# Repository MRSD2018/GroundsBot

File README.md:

# GroundsBot
A ~~flexible~~ system that can perform regular outdoor grounds maintenance tasks such a ~~sidewalk sweeping~~,
~~snow clearing~~ or grass cutting on extreme terrain for use by grounds care ~~and snow removal~~ companies.

This repository is for electrical and mechanical design.  For actual code running on GroundsBot, checkout: https://github.com/MRSD2018/GroundsBot-Software

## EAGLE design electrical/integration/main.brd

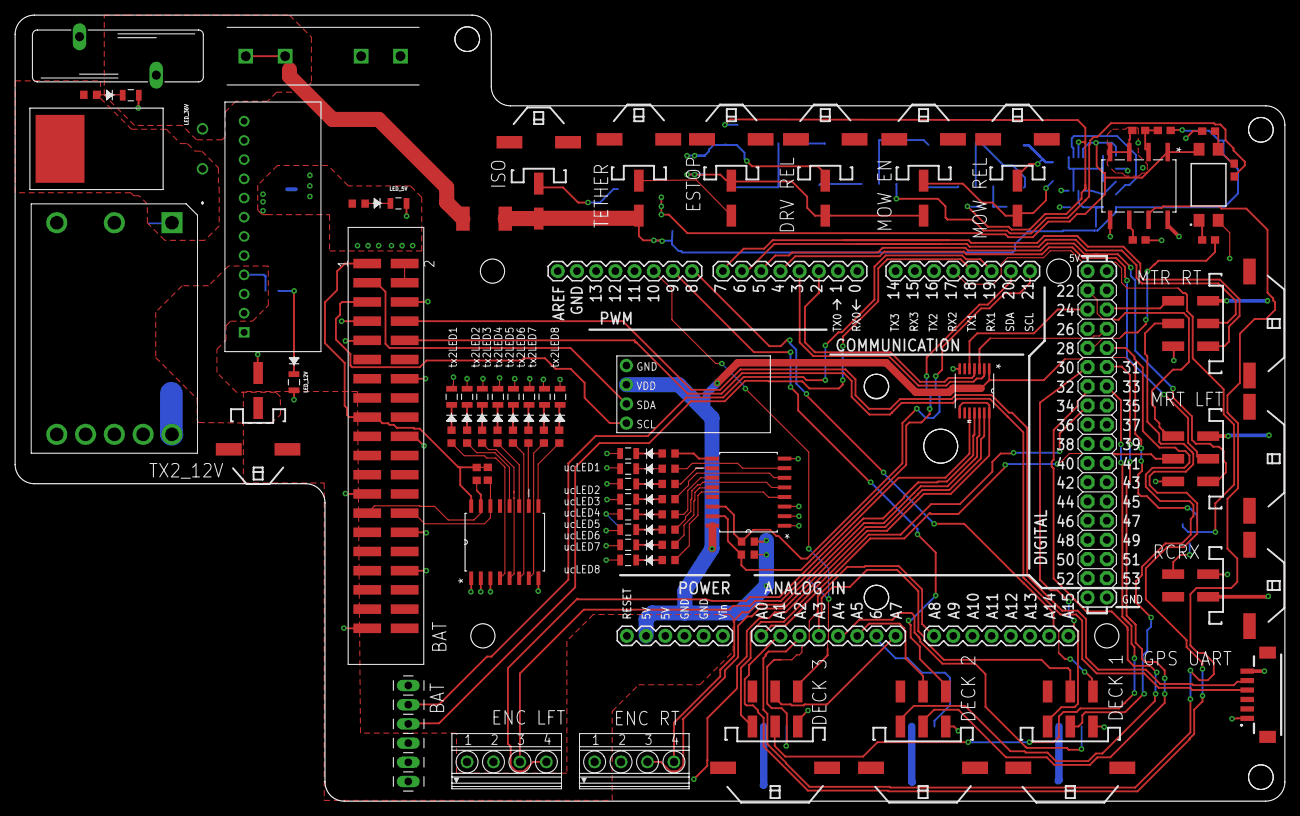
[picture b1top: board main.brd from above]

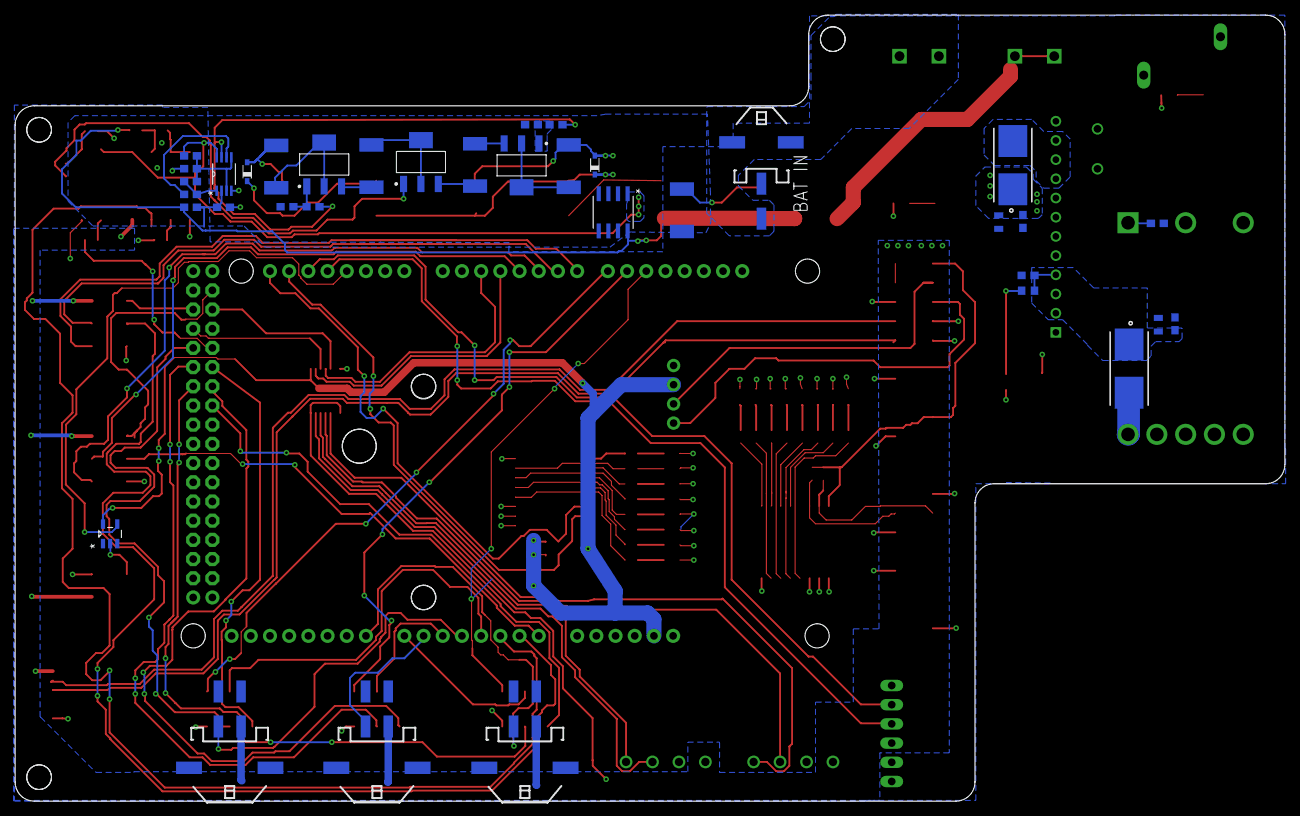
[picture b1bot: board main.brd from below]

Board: 2 copper layers, 168.0 x 104.0 mm, 114 parts (36 on the bottom side), 116 nets.

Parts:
JETSON1:JETSON_J17_UART1:JP3: 61300611121; 1X06
JETSON1:JETSON_TX2_J21_EXPANSION1:LED1, JETSON1:JETSON_TX2_J21_EXPANSION1:LED2, JETSON1:JETSON_TX2_J21_EXPANSION1:LED3, JETSON1:JETSON_TX2_J21_EXPANSION1:LED4, JETSON1:JETSON_TX2_J21_EXPANSION1:LED5, JETSON1:JETSON_TX2_J21_EXPANSION1:LED6, JETSON1:JETSON_TX2_J21_EXPANSION1:LED7, JETSON1:JETSON_TX2_J21_EXPANSION1:LED8: CMD17-21VGD_TR8; LED_CMD17-21VGD_TR8
JETSON1:JETSON_TX2_J21_EXPANSION1:R1, JETSON1:JETSON_TX2_J21_EXPANSION1:R2, JETSON1:JETSON_TX2_J21_EXPANSION1:R3, JETSON1:JETSON_TX2_J21_EXPANSION1:R4, JETSON1:JETSON_TX2_J21_EXPANSION1:R5, JETSON1:JETSON_TX2_J21_EXPANSION1:R6, JETSON1:JETSON_TX2_J21_EXPANSION1:R7, JETSON1:JETSON_TX2_J21_EXPANSION1:R8: 60; R0603
JETSON1:JETSON_TX2_J21_EXPANSION1:R9, JETSON1:JETSON_TX2_J21_EXPANSION1:R10: 10k; R0603
JETSON1:JETSON_TX2_J21_EXPANSION1:U1: PCF8574ATD; SOIC127P1032X265-16N
JETSON1:JETSON_TX2_J21_EXPANSION1:U$3: TSM-120-XX-XXX-DV; TSM-120-XX-XXX-D
MICROCONTROLLER1:LED1, MICROCONTROLLER1:LED2, MICROCONTROLLER1:LED3, MICROCONTROLLER1:LED4, MICROCONTROLLER1:LED5, MICROCONTROLLER1:LED6, MICROCONTROLLER1:LED7, MICROCONTROLLER1:LED8: CMD17-21VGD_TR8; LED_CMD17-21VGD_TR8
MICROCONTROLLER1:R1, MICROCONTROLLER1:R2, MICROCONTROLLER1:R3, MICROCONTROLLER1:R4, MICROCONTROLLER1:R5, MICROCONTROLLER1:R6, MICROCONTROLLER1:R7, MICROCONTROLLER1:R8: 60; R0603
MICROCONTROLLER1:R9, MICROCONTROLLER1:R10: 10k; R0603
MICROCONTROLLER1:U1: PCF8574ATD; SOIC127P1032X265-16N
MICROCONTROLLER1:U$1: ARDUINO_MEGA_R3FULL; ARDUINO_MEGA
MOTOR_TOP1:JDL, MOTOR_TOP1:JDR, MOTOR_TOP1:X3, MOTOR_TOP1:X4, MOTOR_TOP1:X5: 43045-0609
MOTOR_TOP1:X6, MOTOR_TOP1:X7, MOTOR_TOP1:X8: 43045-0409
POWER_TOP1:C1, POWER_TOP1:C3: 1uF; C0603
POWER_TOP1:C2, POWER_TOP1:C4: 100uF; C0603
POWER_TOP1:F1, POWER_TOP1:F2: 0154004.DR; FUSE_0154004.DR
POWER_TOP1:LED1, POWER_TOP1:LED2, POWER_TOP1:LED3: CMD17-21VGD_TR8; LED_CMD17-21VGD_TR8
POWER_TOP1:MOV1: AVR-M2012C120MT6AB; 0805
POWER_TOP1:MOV2: VC080503A100DP; 0805
POWER_TOP1:R2: 495; R0603
POWER_TOP1:R3: 145; R0603
POWER_TOP1:R4: 1695; R0603
POWER_TOP1:U$1: R-745.0P; SIP-12
POWER_TOP1:U$2: V36SE12004NRFA; V36SE12004NRFA-TH
RC_INPUT1:U1: NC7SZ04M5; SOT95P280X145-5N
RC_INPUT1:X1: 43045-0409
RELAY_CONTROL_TOP1:D2: STPS20M60D; TO220AC
RELAY_CONTROL_TOP1:FH3: FUSE_HOLDER_0.205X0.787IN; LF445_0.807IN
RELAY_CONTROL_TOP1:ISO1:R1, RELAY_CONTROL_TOP1:RELAY_CONTROL1:R11, RELAY_CONTROL_TOP1:RELAY_CONTROL1:R13, RELAY_CONTROL_TOP1:RELAY_CONTROL1:UVLO1:R4: 47k; 0603
RELAY_CONTROL_TOP1:ISO1:R2, RELAY_CONTROL_TOP1:ISO1:R5: 330k; 0603
RELAY_CONTROL_TOP1:ISO1:R3, RELAY_CONTROL_TOP1:ISO1:R4, RELAY_CONTROL_TOP1:RELAY_CONTROL1:R1, RELAY_CONTROL_TOP1:RELAY_CONTROL1:R3: 1.20k; 0603
RELAY_CONTROL_TOP1:ISO1:R6: 2.0k; 0603
RELAY_CONTROL_TOP1:ISO1:U1: AMC1200SDUB; DUB8
RELAY_CONTROL_TOP1:ISO1:U2: SFH615A-3X009T; SOIC254P1016X390-4N
RELAY_CONTROL_TOP1:JBAT, RELAY_CONTROL_TOP1:JDC, RELAY_CONTROL_TOP1:JISO, RELAY_CONTROL_TOP1:JMC, RELAY_CONTROL_TOP1:RELAY_CONTROL1:JESTP, RELAY_CONTROL_TOP1:RELAY_CONTROL1:JMOW, RELAY_CONTROL_TOP1:RELAY_CONTROL1:JTHR: 43045-0209
RELAY_CONTROL_TOP1:MOV1: MOV-20D470K; S20K440
RELAY_CONTROL_TOP1:R1, RELAY_CONTROL_TOP1:R2: RES_0R_2512_1W; R2512
RELAY_CONTROL_TOP1:REGULATOR1:U1: LM2936HVMAX-5.0/NOPB; M08A
RELAY_CONTROL_TOP1:RELAY_CONTROL1:D1, RELAY_CONTROL_TOP1:RELAY_CONTROL1:D2: 1N4148WSTR; SOD323_ST
RELAY_CONTROL_TOP1:RELAY_CONTROL1:RCCB1, RELAY_CONTROL_TOP1:RELAY_CONTROL1:RCCB2, RELAY_CONTROL_TOP1:RELAY_CONTROL1:RCCD, RELAY_CONTROL_TOP1:RELAY_CONTROL1:RCCM: RES_52R3_2512_1W_1%; R2512
RELAY_CONTROL_TOP1:RELAY_CONTROL1:U$2, RELAY_CONTROL_TOP1:RELAY_CONTROL1:U$7, RELAY_CONTROL_TOP1:RELAY_CONTROL1:U$10: ZXTN25100DGTA; SOT230P700X160-4N
RELAY_CONTROL_TOP1:RELAY_CONTROL1:UVLO1:R1: 750K; 0603
RELAY_CONTROL_TOP1:RELAY_CONTROL1:UVLO1:R2: 150k; 0603
RELAY_CONTROL_TOP1:RELAY_CONTROL1:UVLO1:R3: 180k; 0603
RELAY_CONTROL_TOP1:RELAY_CONTROL1:UVLO1:R7: 6.8k; 0603
RELAY_CONTROL_TOP1:RELAY_CONTROL1:UVLO1:R8: 75k; 0603
RELAY_CONTROL_TOP1:RELAY_CONTROL1:UVLO1:U1: LMV762MM; SOP65P490X110-8N
SENSOR_TOP1:ENCODER1:X1, SENSOR_TOP1:ENCODER2:X1: 1751264
SENSOR_TOP1:IMU1:U$1: LSM9DS1; SPARKFUN-9DOF-BREAKOUT
SENSOR_TOP1:REACH_GPS1:U$1: DF13-6P-1.25V; DF13C-6P-1.25V
U301: LSF0204PWR; SOP65P640X120-14N
X101: 43045-0209

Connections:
3V3: MICROCONTROLLER1:R9.2, MICROCONTROLLER1:R10.2, MICROCONTROLLER1:U1.16, MICROCONTROLLER1:U$1.3.3V, RC_INPUT1:U1.5, SENSOR_TOP1:IMU1:U$1.VDD, U301.1
5V: MOTOR_TOP1:JDL.P$1, MOTOR_TOP1:JDR.P$1, MOTOR_TOP1:X6.P$1, MOTOR_TOP1:X7.P$1, MOTOR_TOP1:X8.P$1, POWER_TOP1:C4.1, POWER_TOP1:F1.1, POWER_TOP1:MOV2.1, POWER_TOP1:R3.2, RC_INPUT1:X1.P$2, RELAY_CONTROL_TOP1:ISO1:U1.8, SENSOR_TOP1:ENCODER1:X1.1, SENSOR_TOP1:ENCODER2:X1.1, SENSOR_TOP1:REACH_GPS1:U$1.P$6, U301.8, U301.14
5V_ISO: RELAY_CONTROL_TOP1:ISO1:U1.1, RELAY_CONTROL_TOP1:ISO1:U2.4, RELAY_CONTROL_TOP1:REGULATOR1:U1.1, RELAY_CONTROL_TOP1:RELAY_CONTROL1:UVLO1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.2, RELAY_CONTROL_TOP1:RELAY_CONTROL1:UVLO1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.8
12V: MICROCONTROLLER1:U$1.VIN, POWER_TOP1:C2.1, POWER_TOP1:C3.1, POWER_TOP1:F2.1, POWER_TOP1:MOV1.1, POWER_TOP1:R2.2, POWER_TOP1:U$1.VIN1, POWER_TOP1:U$1.VIN2, POWER_TOP1:U$1.VIN3, X101.P$1
36V: POWER_TOP1:C1.1, POWER_TOP1:R4.2, POWER_TOP1:U$2.+VIN, RELAY_CONTROL_TOP1:D2.1, RELAY_CONTROL_TOP1:D2.2
GND: JETSON1:JETSON_J17_UART1:JP3.1, JETSON1:JETSON_TX2_J21_EXPANSION1:LED1.2, JETSON1:JETSON_TX2_J21_EXPANSION1:LED2.2, JETSON1:JETSON_TX2_J21_EXPANSION1:LED3.2, JETSON1:JETSON_TX2_J21_EXPANSION1:LED4.2, JETSON1:JETSON_TX2_J21_EXPANSION1:LED5.2, JETSON1:JETSON_TX2_J21_EXPANSION1:LED6.2, JETSON1:JETSON_TX2_J21_EXPANSION1:LED7.2, JETSON1:JETSON_TX2_J21_EXPANSION1:LED8.2, JETSON1:JETSON_TX2_J21_EXPANSION1:U1.1, JETSON1:JETSON_TX2_J21_EXPANSION1:U1.2, JETSON1:JETSON_TX2_J21_EXPANSION1:U1.3, JETSON1:JETSON_TX2_J21_EXPANSION1:U1.8, JETSON1:JETSON_TX2_J21_EXPANSION1:U$3.6, JETSON1:JETSON_TX2_J21_EXPANSION1:U$3.9, JETSON1:JETSON_TX2_J21_EXPANSION1:U$3.14, JETSON1:JETSON_TX2_J21_EXPANSION1:U$3.20, JETSON1:JETSON_TX2_J21_EXPANSION1:U$3.25, JETSON1:JETSON_TX2_J21_EXPANSION1:U$3.30, JETSON1:JETSON_TX2_J21_EXPANSION1:U$3.34, JETSON1:JETSON_TX2_J21_EXPANSION1:U$3.39, MICROCONTROLLER1:LED1.2, MICROCONTROLLER1:LED2.2, MICROCONTROLLER1:LED3.2, MICROCONTROLLER1:LED4.2, MICROCONTROLLER1:LED5.2, MICROCONTROLLER1:LED6.2, MICROCONTROLLER1:LED7.2, MICROCONTROLLER1:LED8.2, MICROCONTROLLER1:U1.1, MICROCONTROLLER1:U1.2, MICROCONTROLLER1:U1.3, MICROCONTROLLER1:U1.8, MICROCONTROLLER1:U$1.GND@0, MICROCONTROLLER1:U$1.GND@1, MICROCONTROLLER1:U$1.GND@2, MICROCONTROLLER1:U$1.GND@3, MICROCONTROLLER1:U$1.GND@4, MOTOR_TOP1:JDL.P$6, MOTOR_TOP1:JDR.P$6, MOTOR_TOP1:X3.P$1, MOTOR_TOP1:X4.P$1, MOTOR_TOP1:X5.P$1, MOTOR_TOP1:X6.P$3, MOTOR_TOP1:X7.P$3, MOTOR_TOP1:X8.P$3, POWER_TOP1:C1.2, POWER_TOP1:C2.2, POWER_TOP1:C3.2, POWER_TOP1:C4.2, POWER_TOP1:LED1.2, POWER_TOP1:LED2.2, POWER_TOP1:LED3.2, POWER_TOP1:MOV1.2, POWER_TOP1:MOV2.2, POWER_TOP1:U$1.ENABLE, POWER_TOP1:U$1.GND1, POWER_TOP1:U$1.GND2, POWER_TOP1:U$1.GND3, POWER_TOP1:U$1.GND4, POWER_TOP1:U$2.-VIN, POWER_TOP1:U$2.-VOUT, POWER_TOP1:U$2.ENABLE, RC_INPUT1:U1.3, RC_INPUT1:X1.P$1, RELAY_CONTROL_TOP1:ISO1:R2.1, RELAY_CONTROL_TOP1:ISO1:U1.5, RELAY_CONTROL_TOP1:ISO1:U2.2, RELAY_CONTROL_TOP1:JBAT.P$1, RELAY_CONTROL_TOP1:MOV1.2, RELAY_CONTROL_TOP1:R1.2, SENSOR_TOP1:ENCODER1:X1.2, SENSOR_TOP1:ENCODER2:X1.2, SENSOR_TOP1:IMU1:U$1.GND, SENSOR_TOP1:REACH_GPS1:U$1.P$1, U301.7, X101.P$2
GND_ISO: RELAY_CONTROL_TOP1:ISO1:R1.1, RELAY_CONTROL_TOP1:ISO1:R6.1, RELAY_CONTROL_TOP1:ISO1:U1.3, RELAY_CONTROL_TOP1:ISO1:U1.4, RELAY_CONTROL_TOP1:JISO.P$1, RELAY_CONTROL_TOP1:R1.1, RELAY_CONTROL_TOP1:REGULATOR1:U1.2, RELAY_CONTROL_TOP1:REGULATOR1:U1.3, RELAY_CONTROL_TOP1:REGULATOR1:U1.6, RELAY_CONTROL_TOP1:REGULATOR1:U1.7, RELAY_CONTROL_TOP1:RELAY_CONTROL1:R11.2, RELAY_CONTROL_TOP1:RELAY_CONTROL1:R13.2, RELAY_CONTROL_TOP1:RELAY_CONTROL1:RCCD.1, RELAY_CONTROL_TOP1:RELAY_CONTROL1:U$2.3, RELAY_CONTROL_TOP1:RELAY_CONTROL1:UVLO1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.1, RELAY_CONTROL_TOP1:RELAY_CONTROL1:UVLO1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.1, RELAY_CONTROL_TOP1:RELAY_CONTROL1:UVLO1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.4
JETSON1:JETSON_TX2_J21_EXPANSION1:I2C_GP1_CLK_3V3: JETSON1:JETSON_TX2_J21_EXPANSION1:R10.1, JETSON1:JETSON_TX2_J21_EXPANSION1:U1.14, JETSON1:JETSON_TX2_J21_EXPANSION1:U$3.28
JETSON1:JETSON_TX2_J21_EXPANSION1:I2C_GP1_DAT_3V3: JETSON1:JETSON_TX2_J21_EXPANSION1:R9.1, JETSON1:JETSON_TX2_J21_EXPANSION1:U1.15, JETSON1:JETSON_TX2_J21_EXPANSION1:U$3.27
JETSON1:JETSON_TX2_J21_EXPANSION1:N$1: JETSON1:JETSON_TX2_J21_EXPANSION1:LED8.1, JETSON1:JETSON_TX2_J21_EXPANSION1:R8.1
JETSON1:JETSON_TX2_J21_EXPANSION1:N$2: JETSON1:JETSON_TX2_J21_EXPANSION1:LED7.1, JETSON1:JETSON_TX2_J21_EXPANSION1:R7.1
JETSON1:JETSON_TX2_J21_EXPANSION1:N$3: JETSON1:JETSON_TX2_J21_EXPANSION1:LED6.1, JETSON1:JETSON_TX2_J21_EXPANSION1:R6.1
JETSON1:JETSON_TX2_J21_EXPANSION1:N$4: JETSON1:JETSON_TX2_J21_EXPANSION1:LED5.1, JETSON1:JETSON_TX2_J21_EXPANSION1:R5.1
JETSON1:JETSON_TX2_J21_EXPANSION1:N$5: JETSON1:JETSON_TX2_J21_EXPANSION1:LED4.1, JETSON1:JETSON_TX2_J21_EXPANSION1:R4.1
JETSON1:JETSON_TX2_J21_EXPANSION1:N$6: JETSON1:JETSON_TX2_J21_EXPANSION1:LED3.1, JETSON1:JETSON_TX2_J21_EXPANSION1:R3.1
JETSON1:JETSON_TX2_J21_EXPANSION1:N$7: JETSON1:JETSON_TX2_J21_EXPANSION1:LED2.1, JETSON1:JETSON_TX2_J21_EXPANSION1:R2.1
JETSON1:JETSON_TX2_J21_EXPANSION1:N$8: JETSON1:JETSON_TX2_J21_EXPANSION1:LED1.1, JETSON1:JETSON_TX2_J21_EXPANSION1:R1.1
JETSON1:JETSON_TX2_J21_EXPANSION1:N$9: JETSON1:JETSON_TX2_J21_EXPANSION1:R8.2, JETSON1:JETSON_TX2_J21_EXPANSION1:U1.12
JETSON1:JETSON_TX2_J21_EXPANSION1:N$10: JETSON1:JETSON_TX2_J21_EXPANSION1:R7.2, JETSON1:JETSON_TX2_J21_EXPANSION1:U1.11
JETSON1:JETSON_TX2_J21_EXPANSION1:N$11: JETSON1:JETSON_TX2_J21_EXPANSION1:R6.2, JETSON1:JETSON_TX2_J21_EXPANSION1:U1.10
JETSON1:JETSON_TX2_J21_EXPANSION1:N$12: JETSON1:JETSON_TX2_J21_EXPANSION1:R5.2, JETSON1:JETSON_TX2_J21_EXPANSION1:U1.9
JETSON1:JETSON_TX2_J21_EXPANSION1:N$13: JETSON1:JETSON_TX2_J21_EXPANSION1:R4.2, JETSON1:JETSON_TX2_J21_EXPANSION1:U1.7
JETSON1:JETSON_TX2_J21_EXPANSION1:N$14: JETSON1:JETSON_TX2_J21_EXPANSION1:R3.2, JETSON1:JETSON_TX2_J21_EXPANSION1:U1.6
JETSON1:JETSON_TX2_J21_EXPANSION1:N$15: JETSON1:JETSON_TX2_J21_EXPANSION1:R2.2, JETSON1:JETSON_TX2_J21_EXPANSION1:U1.5
JETSON1:JETSON_TX2_J21_EXPANSION1:N$16: JETSON1:JETSON_TX2_J21_EXPANSION1:R1.2, JETSON1:JETSON_TX2_J21_EXPANSION1:U1.4
JETSON1:JETSON_TX2_J21_EXPANSION1:VDD_3V3_SYS: JETSON1:JETSON_TX2_J21_EXPANSION1:R9.2, JETSON1:JETSON_TX2_J21_EXPANSION1:R10.2, JETSON1:JETSON_TX2_J21_EXPANSION1:U1.16, JETSON1:JETSON_TX2_J21_EXPANSION1:U$3.1, JETSON1:JETSON_TX2_J21_EXPANSION1:U$3.17
JETSON1:JETSON_TX2_J21_EXPANSION1:VDD_5V0_IO_SYS: JETSON1:JETSON_TX2_J21_EXPANSION1:U$3.2, JETSON1:JETSON_TX2_J21_EXPANSION1:U$3.4
MICROCONTROLLER1:LED_SCL: MICROCONTROLLER1:R10.1, MICROCONTROLLER1:U1.14, MICROCONTROLLER1:U$1.21
MICROCONTROLLER1:LED_SDA: MICROCONTROLLER1:R9.1, MICROCONTROLLER1:U1.15, MICROCONTROLLER1:U$1.20
MICROCONTROLLER1:N$1: MICROCONTROLLER1:LED8.1, MICROCONTROLLER1:R8.1
MICROCONTROLLER1:N$2: MICROCONTROLLER1:R1.2, MICROCONTROLLER1:U1.4
MICROCONTROLLER1:N$3: MICROCONTROLLER1:LED7.1, MICROCONTROLLER1:R7.1
MICROCONTROLLER1:N$12: MICROCONTROLLER1:LED6.1, MICROCONTROLLER1:R6.1
MICROCONTROLLER1:N$13: MICROCONTROLLER1:LED5.1, MICROCONTROLLER1:R5.1
MICROCONTROLLER1:N$14: MICROCONTROLLER1:LED4.1, MICROCONTROLLER1:R4.1
MICROCONTROLLER1:N$15: MICROCONTROLLER1:LED3.1, MICROCONTROLLER1:R3.1
MICROCONTROLLER1:N$16: MICROCONTROLLER1:LED2.1, MICROCONTROLLER1:R2.1
MICROCONTROLLER1:N$17: MICROCONTROLLER1:LED1.1, MICROCONTROLLER1:R1.1
MICROCONTROLLER1:N$18: MICROCONTROLLER1:R8.2, MICROCONTROLLER1:U1.12
MICROCONTROLLER1:N$19: MICROCONTROLLER1:R7.2, MICROCONTROLLER1:U1.11
MICROCONTROLLER1:N$20: MICROCONTROLLER1:R6.2, MICROCONTROLLER1:U1.10
MICROCONTROLLER1:N$21: MICROCONTROLLER1:R5.2, MICROCONTROLLER1:U1.9
MICROCONTROLLER1:N$22: MICROCONTROLLER1:R4.2, MICROCONTROLLER1:U1.7
MICROCONTROLLER1:N$23: MICROCONTROLLER1:R3.2, MICROCONTROLLER1:U1.6
MICROCONTROLLER1:N$24: MICROCONTROLLER1:R2.2, MICROCONTROLLER1:U1.5
MOW_EN: MICROCONTROLLER1:U$1.28, RELAY_CONTROL_TOP1:ISO1:R3.2
unnamed: MICROCONTROLLER1:U$1.7, MOTOR_TOP1:JDR.P$3
unnamed: JETSON1:JETSON_TX2_J21_EXPANSION1:U$3.10, SENSOR_TOP1:REACH_GPS1:U$1.P$4
unnamed: MICROCONTROLLER1:U$1.22, MOTOR_TOP1:JDL.P$4
unnamed: MICROCONTROLLER1:U$1.A0, MOTOR_TOP1:JDL.P$5
unnamed: MICROCONTROLLER1:U$1.6, MOTOR_TOP1:JDR.P$2
unnamed: JETSON1:JETSON_TX2_J21_EXPANSION1:U$3.8, SENSOR_TOP1:REACH_GPS1:U$1.P$5
unnamed: MICROCONTROLLER1:U$1.25, MOTOR_TOP1:JDR.P$4
unnamed: MICROCONTROLLER1:U$1.A1, MOTOR_TOP1:JDR.P$5
unnamed: MICROCONTROLLER1:U$1.33, MOTOR_TOP1:X5.P$2
unnamed: MICROCONTROLLER1:U$1.34, MOTOR_TOP1:X5.P$3
unnamed: MICROCONTROLLER1:U$1.10, MOTOR_TOP1:X5.P$4
unnamed: MICROCONTROLLER1:U$1.A8, MOTOR_TOP1:X8.P$2
unnamed: MICROCONTROLLER1:U$1.A7, MOTOR_TOP1:X5.P$5
unnamed: MICROCONTROLLER1:U$1.A6, MOTOR_TOP1:X7.P$2
unnamed: MICROCONTROLLER1:U$1.A5, MOTOR_TOP1:X4.P$5
unnamed: MICROCONTROLLER1:U$1.9, MOTOR_TOP1:X4.P$4
unnamed: MICROCONTROLLER1:U$1.32, MOTOR_TOP1:X4.P$3
unnamed: MICROCONTROLLER1:U$1.31, MOTOR_TOP1:X4.P$2
unnamed: JETSON1:JETSON_TX2_J21_EXPANSION1:U$3.5, SENSOR_TOP1:IMU1:U$1.SCL
unnamed: JETSON1:JETSON_TX2_J21_EXPANSION1:U$3.3, SENSOR_TOP1:IMU1:U$1.SDA
unnamed: MICROCONTROLLER1:U$1.A4, MOTOR_TOP1:X6.P$2
unnamed: MICROCONTROLLER1:U$1.A3, MOTOR_TOP1:X3.P$5
unnamed: MICROCONTROLLER1:U$1.8, MOTOR_TOP1:X3.P$4
unnamed: MICROCONTROLLER1:U$1.30, MOTOR_TOP1:X3.P$3
unnamed: MICROCONTROLLER1:U$1.29, MOTOR_TOP1:X3.P$2
unnamed: MICROCONTROLLER1:U$1.5, MOTOR_TOP1:JDL.P$3
unnamed: MICROCONTROLLER1:U$1.4, MOTOR_TOP1:JDL.P$2
unnamed: JETSON1:JETSON_J17_UART1:JP3.5, MICROCONTROLLER1:U$1.19
unnamed: JETSON1:JETSON_J17_UART1:JP3.4, MICROCONTROLLER1:U$1.18
unnamed: MICROCONTROLLER1:U$1.17, RC_INPUT1:U1.4
unnamed: MICROCONTROLLER1:U$1.2, U301.4
unnamed: MICROCONTROLLER1:U$1.24, U301.5
unnamed: MICROCONTROLLER1:U$1.3, U301.2
unnamed: MICROCONTROLLER1:U$1.27, U301.3
POWER_TOP1:N$1: POWER_TOP1:F2.2, POWER_TOP1:U$2.+VOUT
POWER_TOP1:N$2: POWER_TOP1:F1.2, POWER_TOP1:U$1.VOUT1, POWER_TOP1:U$1.VOUT2, POWER_TOP1:U$1.VOUT3
POWER_TOP1:N$3: POWER_TOP1:LED1.1, POWER_TOP1:R4.1
POWER_TOP1:N$4: POWER_TOP1:LED2.1, POWER_TOP1:R2.1
POWER_TOP1:N$5: POWER_TOP1:LED3.1, POWER_TOP1:R3.1
RC_INPUT1:SBUS_SIG_IN: RC_INPUT1:U1.2, RC_INPUT1:X1.P$3
RELAY_CONTROL_TOP1:36V_RAW: RELAY_CONTROL_TOP1:ISO1:R5.2, RELAY_CONTROL_TOP1:JISO.P$2, RELAY_CONTROL_TOP1:R2.1, RELAY_CONTROL_TOP1:REGULATOR1:U1.8, RELAY_CONTROL_TOP1:RELAY_CONTROL1:JTHR.P$2, RELAY_CONTROL_TOP1:RELAY_CONTROL1:UVLO1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.2
RELAY_CONTROL_TOP1:ISO1:N$1: RELAY_CONTROL_TOP1:ISO1:R2.2, RELAY_CONTROL_TOP1:ISO1:U1.6
RELAY_CONTROL_TOP1:ISO1:N$2: RELAY_CONTROL_TOP1:ISO1:R5.1, RELAY_CONTROL_TOP1:ISO1:R6.2, RELAY_CONTROL_TOP1:ISO1:U1.2
RELAY_CONTROL_TOP1:ISO1:N$3: RELAY_CONTROL_TOP1:ISO1:R1.2, RELAY_CONTROL_TOP1:ISO1:R4.2, RELAY_CONTROL_TOP1:ISO1:U2.3
RELAY_CONTROL_TOP1:ISO1:N$4: RELAY_CONTROL_TOP1:ISO1:R3.1, RELAY_CONTROL_TOP1:ISO1:U2.1
RELAY_CONTROL_TOP1:N$1: RELAY_CONTROL_TOP1:FH3.1, RELAY_CONTROL_TOP1:FH3.2, RELAY_CONTROL_TOP1:JBAT.P$2
RELAY_CONTROL_TOP1:N$2: RELAY_CONTROL_TOP1:JMC.P$2, RELAY_CONTROL_TOP1:RELAY_CONTROL1:D2.C, RELAY_CONTROL_TOP1:RELAY_CONTROL1:JMOW.P$1
RELAY_CONTROL_TOP1:N$3: RELAY_CONTROL_TOP1:JDC.P$2, RELAY_CONTROL_TOP1:RELAY_CONTROL1:D1.C, RELAY_CONTROL_TOP1:RELAY_CONTROL1:JESTP.P$1, RELAY_CONTROL_TOP1:RELAY_CONTROL1:JMOW.P$2
RELAY_CONTROL_TOP1:N$4: RELAY_CONTROL_TOP1:JMC.P$1, RELAY_CONTROL_TOP1:RELAY_CONTROL1:D2.A, RELAY_CONTROL_TOP1:RELAY_CONTROL1:RCCB2.2
RELAY_CONTROL_TOP1:N$5: RELAY_CONTROL_TOP1:ISO1:R4.1, RELAY_CONTROL_TOP1:RELAY_CONTROL1:U$2.1
RELAY_CONTROL_TOP1:N$6: RELAY_CONTROL_TOP1:JDC.P$1, RELAY_CONTROL_TOP1:RELAY_CONTROL1:D1.A, RELAY_CONTROL_TOP1:RELAY_CONTROL1:RCCB1.2
RELAY_CONTROL_TOP1:N$11: RELAY_CONTROL_TOP1:D2.3, RELAY_CONTROL_TOP1:FH3.3, RELAY_CONTROL_TOP1:FH3.4, RELAY_CONTROL_TOP1:MOV1.1, RELAY_CONTROL_TOP1:R2.2
RELAY_CONTROL_TOP1:RELAY_CONTROL1:!UVLO!: RELAY_CONTROL_TOP1:RELAY_CONTROL1:R1.1, RELAY_CONTROL_TOP1:RELAY_CONTROL1:R3.1, RELAY_CONTROL_TOP1:RELAY_CONTROL1:UVLO1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.7
RELAY_CONTROL_TOP1:RELAY_CONTROL1:N$1: RELAY_CONTROL_TOP1:RELAY_CONTROL1:JESTP.P$2, RELAY_CONTROL_TOP1:RELAY_CONTROL1:JTHR.P$1
RELAY_CONTROL_TOP1:RELAY_CONTROL1:N$2: RELAY_CONTROL_TOP1:RELAY_CONTROL1:RCCM.1, RELAY_CONTROL_TOP1:RELAY_CONTROL1:U$2.2, RELAY_CONTROL_TOP1:RELAY_CONTROL1:U$2.4
RELAY_CONTROL_TOP1:RELAY_CONTROL1:N$5: RELAY_CONTROL_TOP1:RELAY_CONTROL1:RCCB2.1, RELAY_CONTROL_TOP1:RELAY_CONTROL1:U$7.2, RELAY_CONTROL_TOP1:RELAY_CONTROL1:U$7.4
RELAY_CONTROL_TOP1:RELAY_CONTROL1:N$6: RELAY_CONTROL_TOP1:RELAY_CONTROL1:RCCM.2, RELAY_CONTROL_TOP1:RELAY_CONTROL1:U$7.3
RELAY_CONTROL_TOP1:RELAY_CONTROL1:N$7: RELAY_CONTROL_TOP1:RELAY_CONTROL1:R3.2, RELAY_CONTROL_TOP1:RELAY_CONTROL1:R11.1, RELAY_CONTROL_TOP1:RELAY_CONTROL1:U$10.1
RELAY_CONTROL_TOP1:RELAY_CONTROL1:N$9: RELAY_CONTROL_TOP1:RELAY_CONTROL1:RCCD.2, RELAY_CONTROL_TOP1:RELAY_CONTROL1:U$10.3
RELAY_CONTROL_TOP1:RELAY_CONTROL1:N$10: RELAY_CONTROL_TOP1:RELAY_CONTROL1:RCCB1.1, RELAY_CONTROL_TOP1:RELAY_CONTROL1:U$10.2, RELAY_CONTROL_TOP1:RELAY_CONTROL1:U$10.4
RELAY_CONTROL_TOP1:RELAY_CONTROL1:N$11: RELAY_CONTROL_TOP1:RELAY_CONTROL1:R1.2, RELAY_CONTROL_TOP1:RELAY_CONTROL1:R13.1, RELAY_CONTROL_TOP1:RELAY_CONTROL1:U$7.1
RELAY_CONTROL_TOP1:RELAY_CONTROL1:UVLO1:N$2: RELAY_CONTROL_TOP1:RELAY_CONTROL1:UVLO1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.1, RELAY_CONTROL_TOP1:RELAY_CONTROL1:UVLO1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.6
RELAY_CONTROL_TOP1:RELAY_CONTROL1:UVLO1:N$3: RELAY_CONTROL_TOP1:RELAY_CONTROL1:UVLO1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.1, RELAY_CONTROL_TOP1:RELAY_CONTROL1:UVLO1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.1, RELAY_CONTROL_TOP1:RELAY_CONTROL1:UVLO1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.2, RELAY_CONTROL_TOP1:RELAY_CONTROL1:UVLO1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.3, RELAY_CONTROL_TOP1:RELAY_CONTROL1:UVLO1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.5
RELAY_CONTROL_TOP1:RELAY_CONTROL1:UVLO1:N$4: RELAY_CONTROL_TOP1:RELAY_CONTROL1:UVLO1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.2, RELAY_CONTROL_TOP1:RELAY_CONTROL1:UVLO1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.1, RELAY_CONTROL_TOP1:RELAY_CONTROL1:UVLO1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.2
RELAY_CONTROL_TOP1:RELAY_CONTROL1:UVLO1:UVLO: RELAY_CONTROL_TOP1:RELAY_CONTROL1:UVLO1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.2, RELAY_CONTROL_TOP1:RELAY_CONTROL1:UVLO1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.2, RELAY_CONTROL_TOP1:RELAY_CONTROL1:UVLO1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.1
SENSOR_TOP1:N$1: SENSOR_TOP1:ENCODER1:X1.3, U301.13
SENSOR_TOP1:N$2: SENSOR_TOP1:ENCODER1:X1.4, U301.12
SENSOR_TOP1:N$3: SENSOR_TOP1:ENCODER2:X1.3, U301.11
SENSOR_TOP1:N$4: SENSOR_TOP1:ENCODER2:X1.4, U301.10
VSENSE: MICROCONTROLLER1:U$1.A2, RELAY_CONTROL_TOP1:ISO1:U1.7

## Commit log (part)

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2017-09-03 init directory structure
2017-09-05 Initial mechanical directory structure and platform files.
2017-09-24 create codr template
2017-09-25 add draft 2 objectives tree
2017-09-25 add m.n.3
2017-09-27 added subsystems
2017-09-27 update cyberphysical diagram. add cyberphysical text. format image placement
2017-09-28 add pm section
2017-09-28 started tables, finished subsystems
2017-09-28 tables are pretty
2017-09-28 files for functional architecture.
2017-09-28 shrunk tables
2017-09-28 Sys Req Table
    Finally figured out how to make a pretty table for system requirments. Go me!
2017-09-28 Updated BOM table
2017-09-28 fixed table spacing
2017-09-28 add project description
2017-09-28 Sys Reqs done
    lookin real purty
2017-09-29 hip minimal tables
2017-09-29 more pretty charts
2017-09-29 some unH'd tables
2017-09-29 Updates to tables to make headings bold and lines consistent, inserted groundsbot logo.
2017-09-29 Shuffled Sys Reqs Around. Standardized language used
2017-09-29 Killing functional requirements again
    How does it keep popping up where it doesn't belong??
2017-09-29 Fixing alignment on my tables
2017-09-29 Added an intro to Sys Reqs
    Might not be coherent...I'm tired
2017-09-29 sections start on new page
2017-09-29 fixed table title spacing
2017-09-29 add references
2017-09-29 remade pdf
2017-09-29 Makin pretty lists. Added indentfirst
2017-09-29 update reference section headers
2017-09-29 add risk management thx david
2017-09-29 Misc wording edits
2017-09-29 table titles back
2017-09-29 risk management table beautified
2017-09-29 use case pic1
2017-09-29 Use Case Pic 2
2017-09-29 fixed paragraph spacing
2017-09-29 Validation experiments in list form
2017-09-29 added codr subtitle
2017-09-29 add sponsor to title. remvoe floating groundsbot. refactor project description
2017-09-29 added usecase pics
2017-09-29 added images
2017-09-29 removed pdf
2017-09-29 Groundsbot 2 GroundsBot
2017-09-29 added usecase text
2017-09-29 remove rogue groundsbot
2017-09-29 add trade study text
2017-09-29 Revert "add trade study text"
    This reverts commit 340abbacb5c492d5b56f113c05e4860a36fbdd05.
2017-09-29 Revert "Merge branch 'codr' of https://github.com/MRSD2017/GroundsBot into codr"
    This reverts commit 2300cb78b1f64da5ed69180274f07d89a8b673f3, reversing
    changes made to 6f319930390cbd75e13a5aeb5ca7f1524afc1890.
2017-09-29 Revert "added usecase text"
    This reverts commit 6f319930390cbd75e13a5aeb5ca7f1524afc1890.
2017-09-29 use case fixed
2017-09-29 reimplement trade study text
2017-09-29 missing period
2017-09-29 Updated the configuration table
2017-09-29 FIXED ARROWS!!!!!
2017-09-30 table headers to arial
2017-09-30 update RGBD text and fix RGBD table
2017-09-30 Cyberphysical architecture as a pdf with updates.
2017-09-30 New Cyberphysical
2017-09-30 wifi is WiFi. add gps base station to cyberphysical
2017-09-30 fixed project milestone spacing
2017-09-30 moved progress reviews to progress review
2017-09-30 Minor change to correct platform configuration image size
2017-09-30 Added description of the BOM.
2017-09-30 Spring validation change to avoid a part a).
2017-09-30 resize table headers
2017-09-30 merged
2017-09-30 schedule remove milestone wordage
2017-09-30 period
2017-09-30 fixed figure captions
2017-09-30 fix typos validation test
2017-09-30 update team roles and format
2017-09-30 added bold
2017-09-30 Revert "added bold"
    This reverts commit dbfd267791d53b66bb16c2966e58543275e131f0.
2017-09-30 NO MORE BOLD ON TABLE 10
2017-09-30 spellcheck
2017-09-30 enforce single space after period
2017-09-30 Updated narrative.
2017-09-30 moved autonomy paragraph down
2017-09-30 Revert "moved autonomy paragraph down"
    This reverts commit d9c87e374ea2054a88c3e5963a6f4ab183ede525.
2017-09-30 add newpage to group text
2017-09-30 break spring validation new page
2017-10-02 Created an icon for the website.
2017-10-02 Added icon image and background for website content.
2017-10-06 added weldments
2017-10-07 Updates to motor calculations and the platform bom.xlsx
2017-10-07 Added a model for the motor.
2017-10-07 Added wheel assemblies, renamed extrusion base, designed wheel mounting.
2017-10-07 added chassis
2017-10-07 added other chassis parts
2017-10-07 added chassis_subassembly to frame_assembly
2017-10-07 Created a top level platform assembly, fixed some issues with the chassis sub assembly
2017-10-07 updated chassis_assembly to use same sketch
2017-10-07 Changed the assembly hierarchy, fixed weldments and locked down some derived sketches.
2017-10-07 Fixes to the main assembly, added mower blade. Added custom extrusions folder and instructions for how to get solidworks to reference them properly.
2017-10-07 Modifications to extrusion selection.
2017-10-07 Changes to main frame and reconfiguring wheel positions.
2017-10-07 changed main frame to use 3d sketc
2017-10-07 added color to wheels
2017-10-07 Created electrical panels and updated weldments with covers and ducts.
2017-10-07 Updates to the frame and integration of electrical panels.
2017-10-07 Updated electrical panel shape and position.
2017-10-07 Added gear motor bracket.
2017-10-08 Added angle brackets to top extrusion and brackets for caster
2017-10-08 Updates to main frame to add corner extrusions, improved caster brackets. Added mounting hardware for 8020.
2017-10-08 added cover loft
2017-10-08 arrange sch submodules.
2017-10-10 closed lids
2017-10-15 init ee bom top
2017-10-17 Updated frame and did FEA analysis on motor mounts.
2017-10-17 init integration
2017-10-17 Updated model for mowing platform, continued work on frame. Modelled battery.
2017-10-17 clear j26
2017-10-17 add pinout to J26
2017-10-17 add J21 pinout
2017-10-17 clean imu
2017-10-17 add stepper pinout
2017-10-17 power pinouts
2017-10-17 rearange top level
2017-10-18 module arrangment updated
2017-10-18 Updated frame with new cross member. LAST COMMIT BEFORE SWITCHING FROM 15 to 10 for extrusions.
2017-10-18 add netfile gen script. add header libraries. TSM-115 incomplete
2017-10-18 edit TSM-120 to be 30 pin TSM-115
2017-10-18 Electrical panel layout work.
2017-10-18 Adding the Arduino due library
2017-10-19 Adding pin names and ports to microcontroller
2017-10-19 add 12V DC-Dc V36SE12004NRFA
2017-10-19 add 5V DC-DC R-745.0P
2017-10-19 Connecting microcontroller, motor, and sensor module with wires
2017-10-19 Microcontroller wires added and RC IN module added
2017-10-19 Work on electrical panel.
2017-10-19 Finalizing BOM, altering alignment of components. Added stand for Zed camera.
2017-10-19 added software submodule
2017-10-21 fix broken fig references, required recompile
2017-10-21 remove old prd. add requirements, raw text from codr
2017-10-21 update requirements per codr feedback
2017-10-21 revert requirements on this branch
2017-10-21 Updates to include all hole positions.
2017-10-21 update validation per new requirements
2017-10-21 add line because github dumb
2017-10-22 init relay
2017-10-22 complete DG85BM relay lib component
2017-10-22 add coil drive npn
2017-10-22 add reed switch
2017-10-22 Add toggle switch library from snapeda
2017-10-22 add add digital optoisolator from snapeda
2017-10-22 swap isolator for in stock part
2017-10-22 add led lib
2017-10-22 add fuses to top bom. Add 25A fuse holder to lib
2017-10-22 add 5x20mm fuse holder
2017-10-22 eagle is dumb, adding power rails to library
2017-10-23 start hot things pcba
2017-10-23 add comparator lib
2017-10-23 recommit requirements
2017-10-23 fix req references to other reqs
2017-10-23 Remove report generation from SVE test 1
2017-10-23 We, uh, dont need the soccer ball for SVE test 3
2017-10-24 1/8th acre req. Adam talking notes
2017-10-24 Connections to TX2
2017-10-24 FVE WBS down to 1 slide
2017-10-24 add 10.16mm connector
2017-10-24 make stupid diode symbol look like a diode. add power connectors to sch
2017-10-24 led control added
2017-10-24 fixing merge of CM17-21VGD library
2017-10-25 add power diode. move relays off board
2017-10-25 spec power for coil drive components. spec uvlo hysteresis.
2017-10-25 update frame titles stupid eagle
2017-10-25 add 2pos molex microfit
2017-10-25 add 6pos molex microfit
2017-10-25 IMU connectors added, ready to merge
2017-10-26 getting ready to merge with Joe
2017-10-26 add molex connector lib again
2017-10-26 retreive libs from 2become1 branch
2017-10-26 clear ERC
2017-10-26 replace reed switch with breakout connector
2017-10-26 add littelfuse 0154004 holder
2017-10-26 add fuse holder to bom
2017-10-26 add MOVs to 5V and 12V rail
2017-10-26 add MOV to bat in
2017-10-26 display mov descriptions on sch
2017-10-27 clean top level wiring
2017-10-27 Work on electrical panel layout.
2017-10-27 Mechanical inputs for breakout board.
2017-10-27 integration/main.sch
    clean more wires
2017-10-28 Hole dimensions and callouts for the electrical panel
2017-10-29 added power line and leds in my review
2017-10-29 Rendering file for presentation.
2017-10-30 clean +5V erroneous vdd symbols. clean mismatched nets on DUE breakouts
2017-10-30 add rc filter iso current sense out
2017-10-30 add hirose con to Reach gps. swap and relabel uart lines from jetson to reach for clarity
2017-10-30 swap ground on motor controller con to align wires
2017-10-31 Switched SBUS on RX0 to SBUS on RX2
2017-10-31 Switch SBUS from RX0 to RX2, and connected all arduino grounds
2017-10-31 add dxfs and reference mechanical drawings for layout. import connectors positions
2017-11-01 update dxfs extend board outline
2017-11-01 Updates to the mechanical inputs for the PCB.
2017-11-01 Updated bottom connector position dxf file.
2017-11-01 group components logically
2017-11-01 remove extraneous headers
2017-11-01 replace mow enable toggle with connector. position connectors more
2017-11-01 make output connector names more clearer
2017-11-01 swap coil drive connector polarity for consistency with other connectors
2017-11-01 move motor encoders to arduino mega interrupts
2017-11-01 add missing npn base resistor mow en
2017-11-02 1st draft connector placement
2017-11-02 update dxf
2017-11-02 incremental more wires
2017-11-02 import new dxf
2017-11-02 connected non-pwr signals
2017-11-02 sweeeet 5V polygonzzzz
2017-11-02 12V polygon
2017-11-02 all connected
2017-11-02 clear width errors
2017-11-02 clear top bot clearance issues
2017-11-02 increment
2017-11-03 seriously why do eagle users put silkscreen over pads in library components?
2017-11-03 clear drc
2017-11-03 clean routing
2017-11-03 fix broken motor schematic links, ipso facto added to PCB
2017-11-03 Progress on redesigning electrical panel for additional relays.
2017-11-04 Updating pcb with new connector positions.
2017-11-04 Adding new connectors on pcb.
2017-11-04 Update experiments per preliminary design review
2017-11-04 update stop time
2017-11-05 sync part attributes for manufacturer and mpn
2017-11-06 add gerber output job
2017-11-06 convert mounting hole outlines to actual holes
2017-11-06 track gerber manufacturing files
2017-11-07 Finalizing drawings for electrical panel production, PCIE bracket design revision and new drawing.
2017-11-07 more resistors
2017-11-07 add 750k
2017-11-07 add capacitors
2017-11-07 replace fuse
2017-11-07 add 33V MOV
2017-11-07 add fuse bom item
2017-11-07 updated BOM
2017-11-07 add order bom, manual edit
2017-11-13 Speed measurements and IMU orientation matrix measurements.
2017-11-15 update offline grass classification test procedure
2017-11-16 update gps criteria for clarity
2017-11-16 Added a roll cage and adjusted the wheel positions.
2017-11-22 Changed roll cage per actual positioning and height.
2017-12-05 Added missing fastener.
2017-12-07 critical design review init, clone from conceptual design review
2017-12-07 init merging new sections into cdr
2017-12-12 backup from overleaf
2018-01-26 Software architecture diagram
2018-03-12 Updated CAD files for bumblebee location. adding various media files.
2018-05-02 Initial commit - pulling over from fall cdr.

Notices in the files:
parts and their libraries:
SparkFun-Resistors: Licensing: Creative Commons ShareAlike 4.0 International - https://creativecommons.org/licenses/by-sa/4.0
